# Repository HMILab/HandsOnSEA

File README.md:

# HandsOn-SEA

HandsOn-SEA is a single degree of freedom educational robot that features series elastic actuation and relies on closed loop force control to achieve the desired level of safety and transparency during physical interactions. HandsOn-SEA complements the existing impedance-type Haptic Paddle designs by demonstrating the challenges involved in the synergistic design and control of admittance-type devices. HandsOn-SEA can be used to allow students to experience the performance trade-offs inherent in force control systems, due to the non-collocation between the force sensor and the actuator.

For more information and videos please follow the [link](http://hmi.sabanciuniv.edu/?page_id=992).

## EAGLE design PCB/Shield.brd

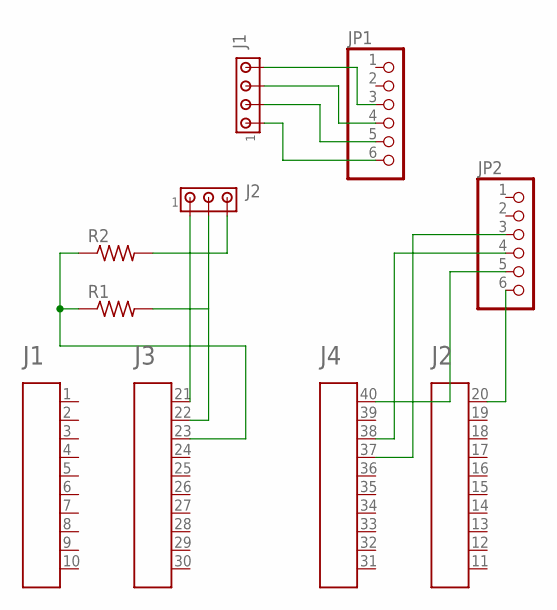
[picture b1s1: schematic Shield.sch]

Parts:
A1: HEADER4X10-BOOSTERPACK; 4X10-BOOSTERPACK
J1: MTA04-156; 1X4MTA
J2: MTA03-156; 1X3MTA
JP1, JP2: PINHD-1X6; 1X06
R1, R2: R-US_0207/10; 0207/10

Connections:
unnamed: A1.20, JP2.6
unnamed: A1.40, JP2.5
unnamed: A1.37, JP2.3
unnamed: A1.38, JP2.4
unnamed: A1.21, J2.1
unnamed: J1.1, JP1.6
unnamed: J1.2, JP1.5
unnamed: J1.3, JP1.4
unnamed: J1.4, JP1.3
unnamed: J2.3, R2.2
unnamed: A1.22, J2.2, R1.2
unnamed: A1.23, R1.1, R2.1

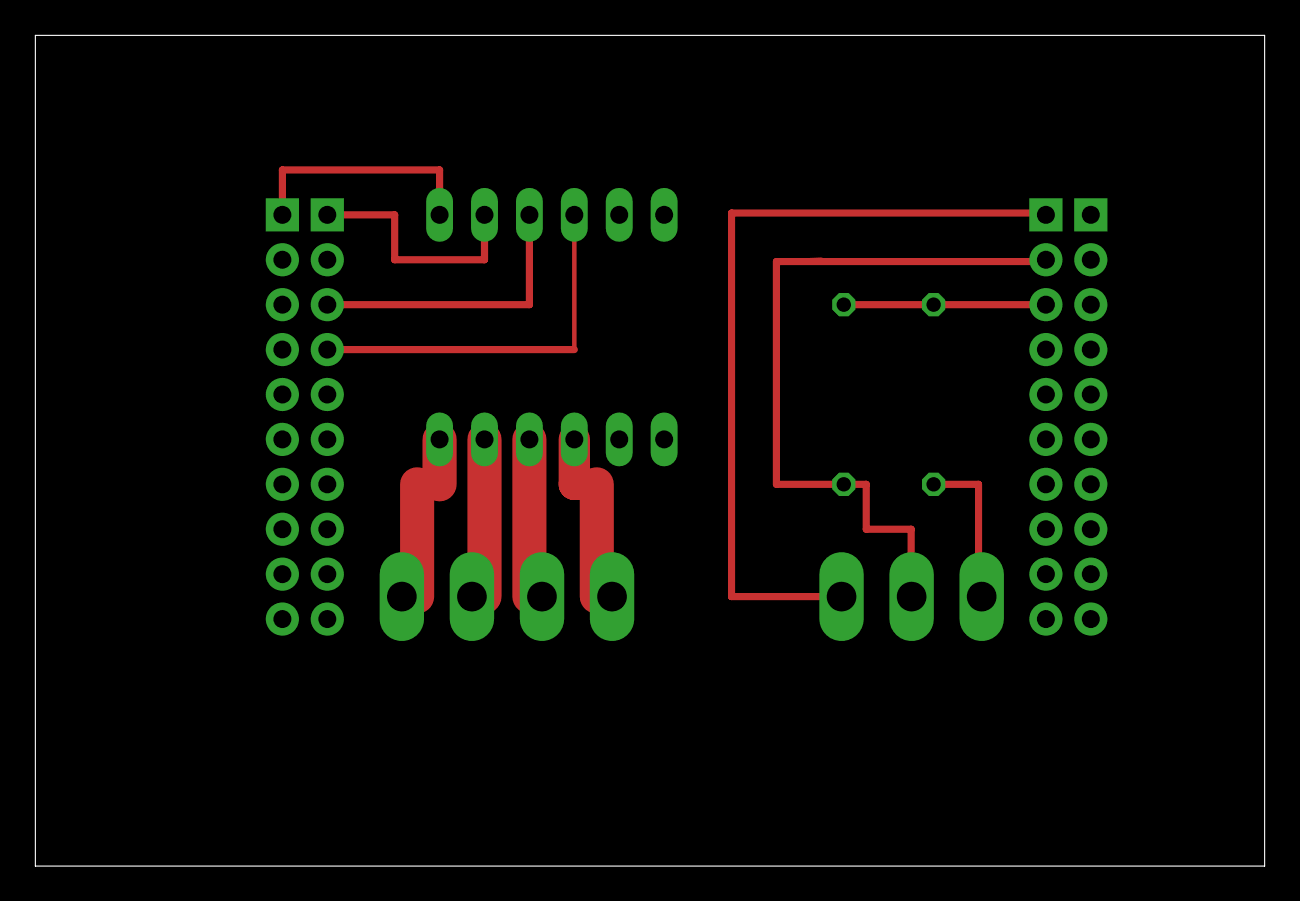
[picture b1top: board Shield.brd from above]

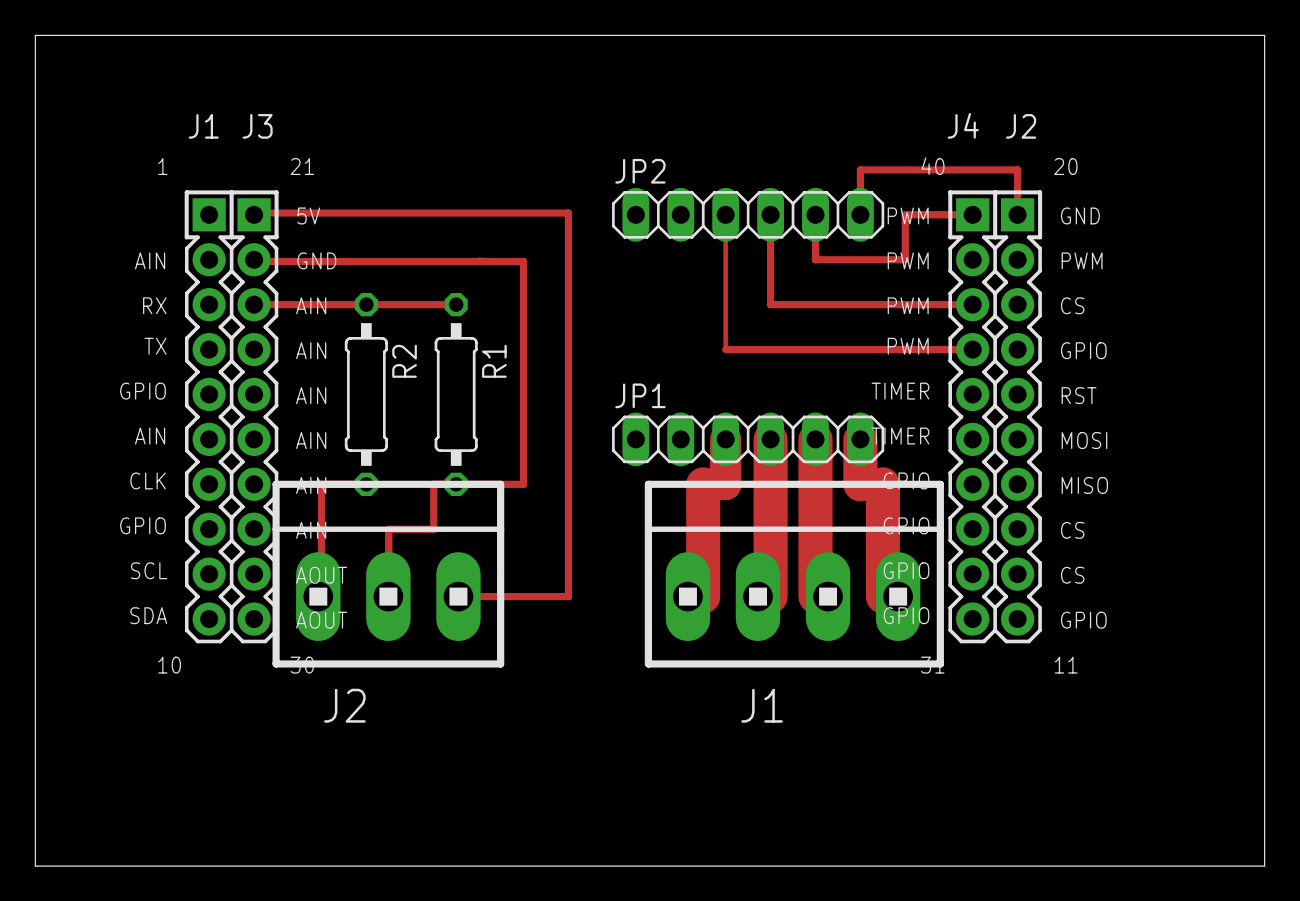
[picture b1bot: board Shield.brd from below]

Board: 2 copper layers, 69.5 x 47.0 mm, 7 parts (7 on the bottom side), 12 nets.

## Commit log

2017-11-19 Initial Commit - Manufacturing files
2017-11-19 Build guide is added
2017-11-19 Acrobat warning.
2018-03-16 Matlab and Simulink files added.
2018-11-16 Lab manual added
